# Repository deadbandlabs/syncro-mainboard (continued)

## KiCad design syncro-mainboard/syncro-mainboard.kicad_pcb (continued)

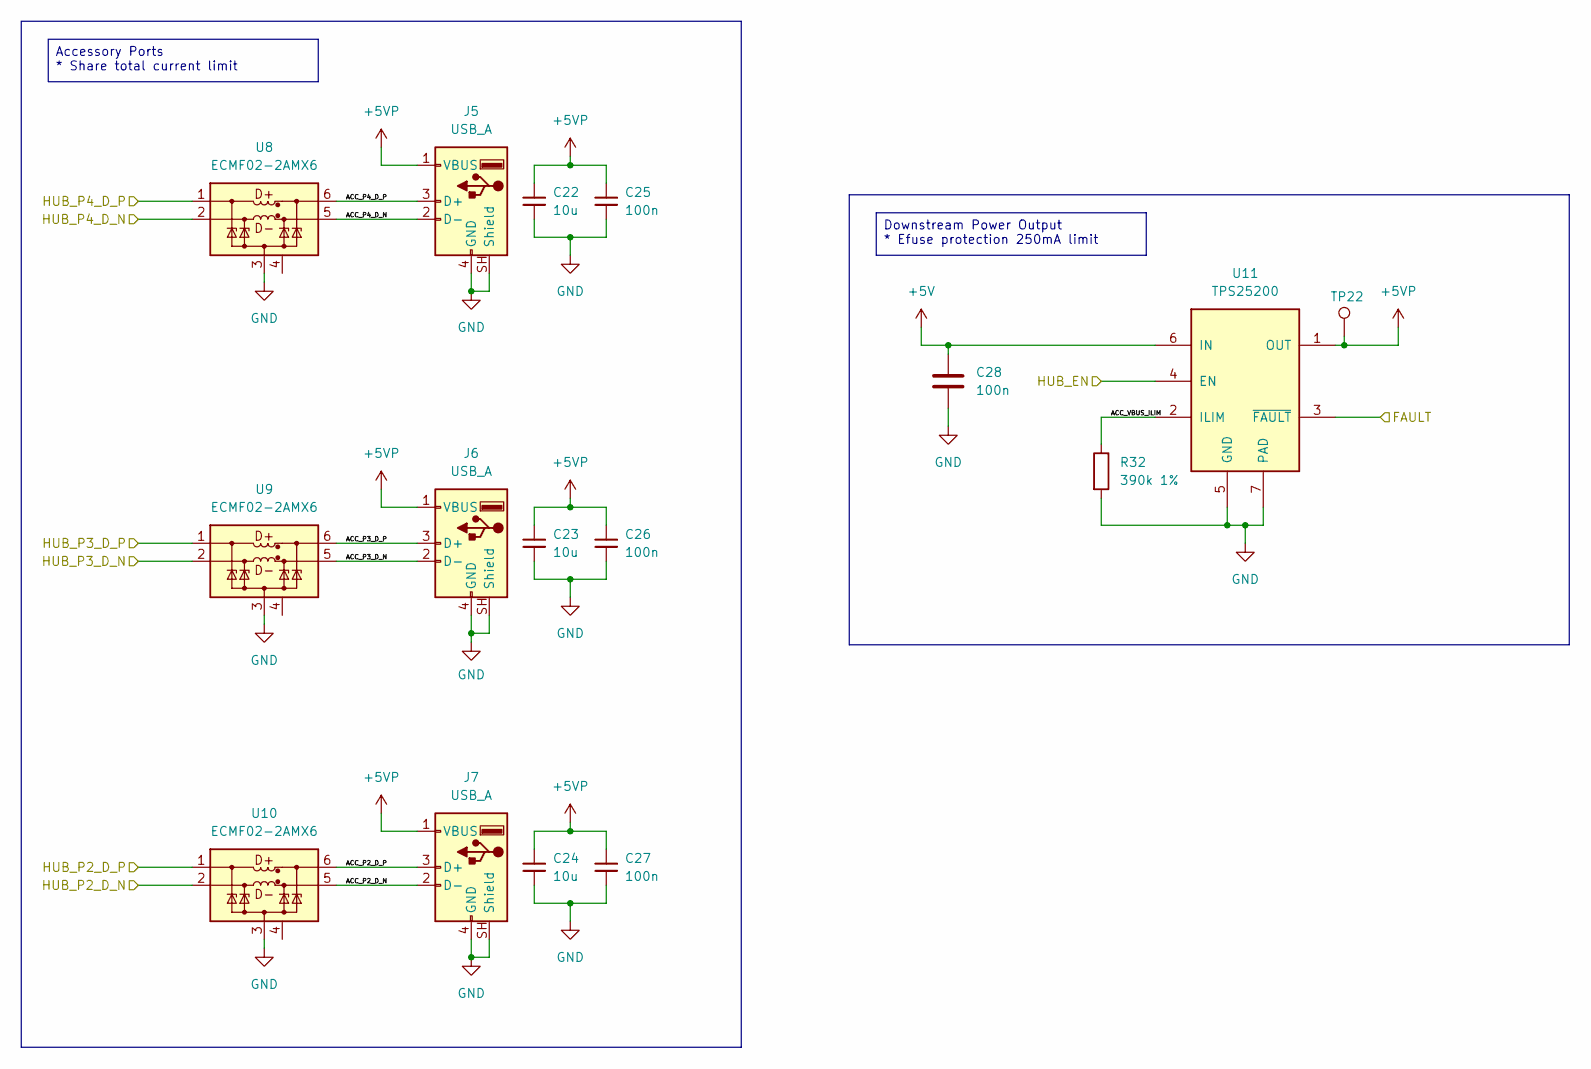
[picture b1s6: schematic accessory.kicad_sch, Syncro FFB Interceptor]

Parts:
C22, C23, C24: 10u; C_0805_2012Metric; LCSC C15850
C25, C26, C27, C28: 100n; C_0402_1005Metric; LCSC C1525
J5, J6, J7: USB_A; USB_A_SHOUHAN_10.0-QTJ6.3_Horizontal; LCSC C404966
R32: 390k 1%; R_0402_1005Metric; LCSC C25782
TP22: VUSB; TestPoint_Pad_D1.5mm
U8, U9, U10: ECMF02-2AMX6; ST_UQFN-6L_1.5x1.7mm_P0.5mm; MPN ECMF02-2AMX6; LCSC C2651144
U11: TPS25200; WSON-6-1EP_2x2mm_P0.65mm_EP1x1.6mm_ThermalVias_0.3mm; MPN TPS25200DRVR; LCSC C128401

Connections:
+5V: C28.1, U11.6 (IN); also elsewhere on the board
+5VP: C22.1, C23.1, C24.1, C25.1, C26.1, C27.1, J5.1 (VBUS), J6.1 (VBUS), J7.1 (VBUS), TP22.1 (1_1), U11.1 (OUT)
/STM32MP13 SOM/HUB_EN: U11.4 (EN); also elsewhere on the board
/USB Mux/HUB_FAULT: U11.3 (~FAULT); also elsewhere on the board
/USB Mux/USB Accessory Ports/ACC_P2_D_N: J7.2 (D-), U10.5 (D-_out)
/USB Mux/USB Accessory Ports/ACC_P2_D_P: J7.3 (D+), U10.6 (D+_out)
/USB Mux/USB Accessory Ports/ACC_P3_D_N: J6.2 (D-), U9.5 (D-_out)
/USB Mux/USB Accessory Ports/ACC_P3_D_P: J6.3 (D+), U9.6 (D+_out)
/USB Mux/USB Accessory Ports/ACC_P4_D_N: J5.2 (D-), U8.5 (D-_out)
/USB Mux/USB Accessory Ports/ACC_P4_D_P: J5.3 (D+), U8.6 (D+_out)
/USB Mux/USB Accessory Ports/ACC_VBUS_ILIM: R32.1, U11.2 (ILIM)
/USB Mux/USB Accessory Ports/HUB_P2_D_N: U10.2 (D-_in); also elsewhere on the board
/USB Mux/USB Accessory Ports/HUB_P2_D_P: U10.1 (D+_in); also elsewhere on the board
/USB Mux/USB Accessory Ports/HUB_P3_D_N: U9.2 (D-_in); also elsewhere on the board
/USB Mux/USB Accessory Ports/HUB_P3_D_P: U9.1 (D+_in); also elsewhere on the board
/USB Mux/USB Accessory Ports/HUB_P4_D_N: U8.2 (D-_in); also elsewhere on the board
/USB Mux/USB Accessory Ports/HUB_P4_D_P: U8.1 (D+_in); also elsewhere on the board
GND: C22.2, C23.2, C24.2, C25.2, C26.2, C27.2, C28.2, J5.4 (GND), J5.SH (Shield), J6.4 (GND), J6.SH (Shield), J7.4 (GND), J7.SH (Shield), R32.2, U8.3 (GND), U9.3 (GND), U10.3 (GND), U11.5 (GND), U11.7 (PAD); also elsewhere on the board

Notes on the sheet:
Accessory Ports * Share total current limit
Downstream Power Output * Efuse protection 250mA limit

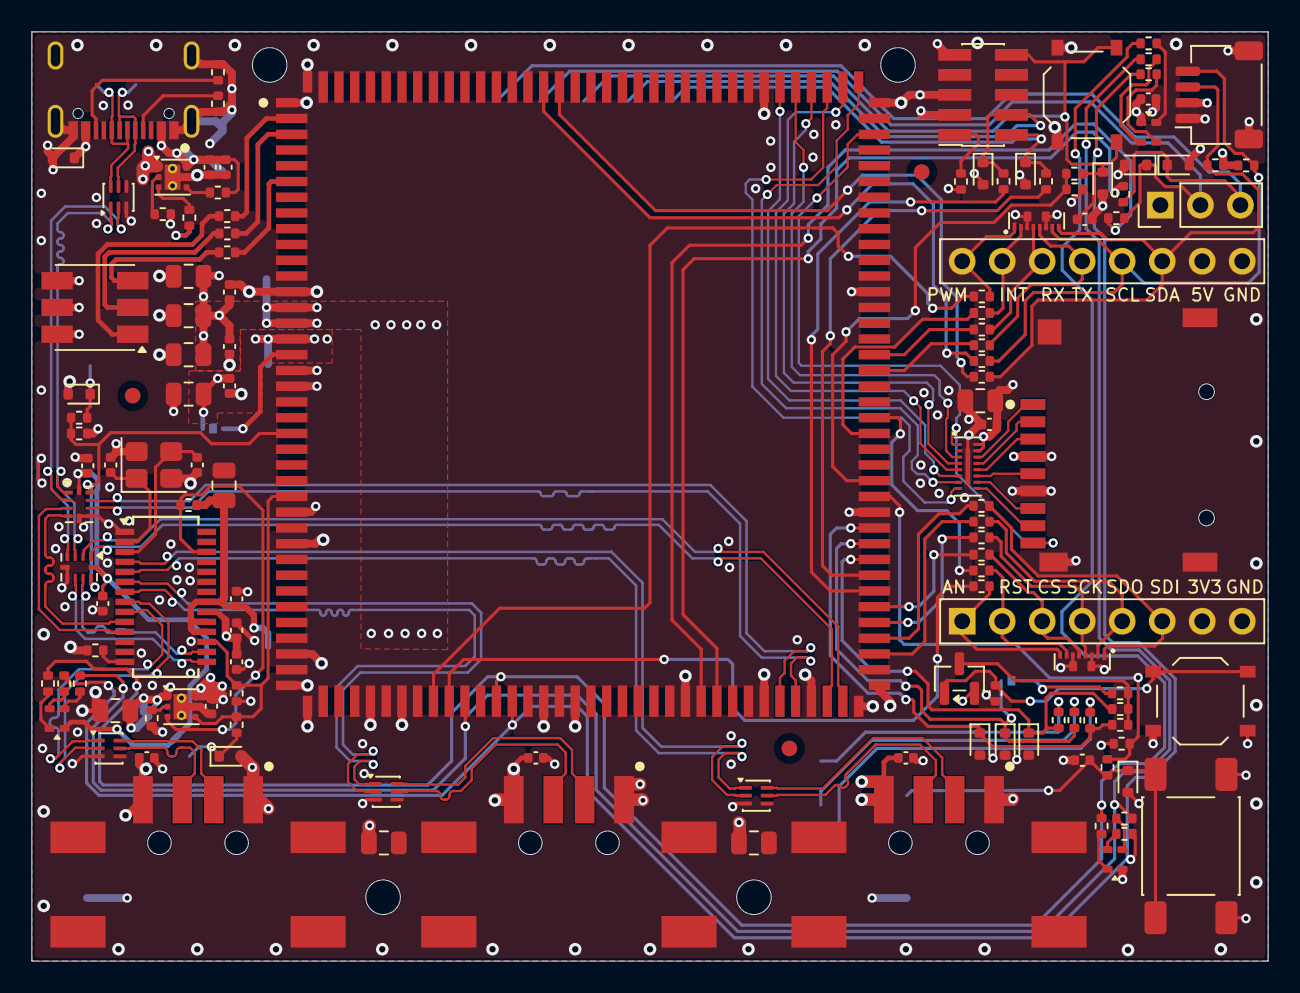
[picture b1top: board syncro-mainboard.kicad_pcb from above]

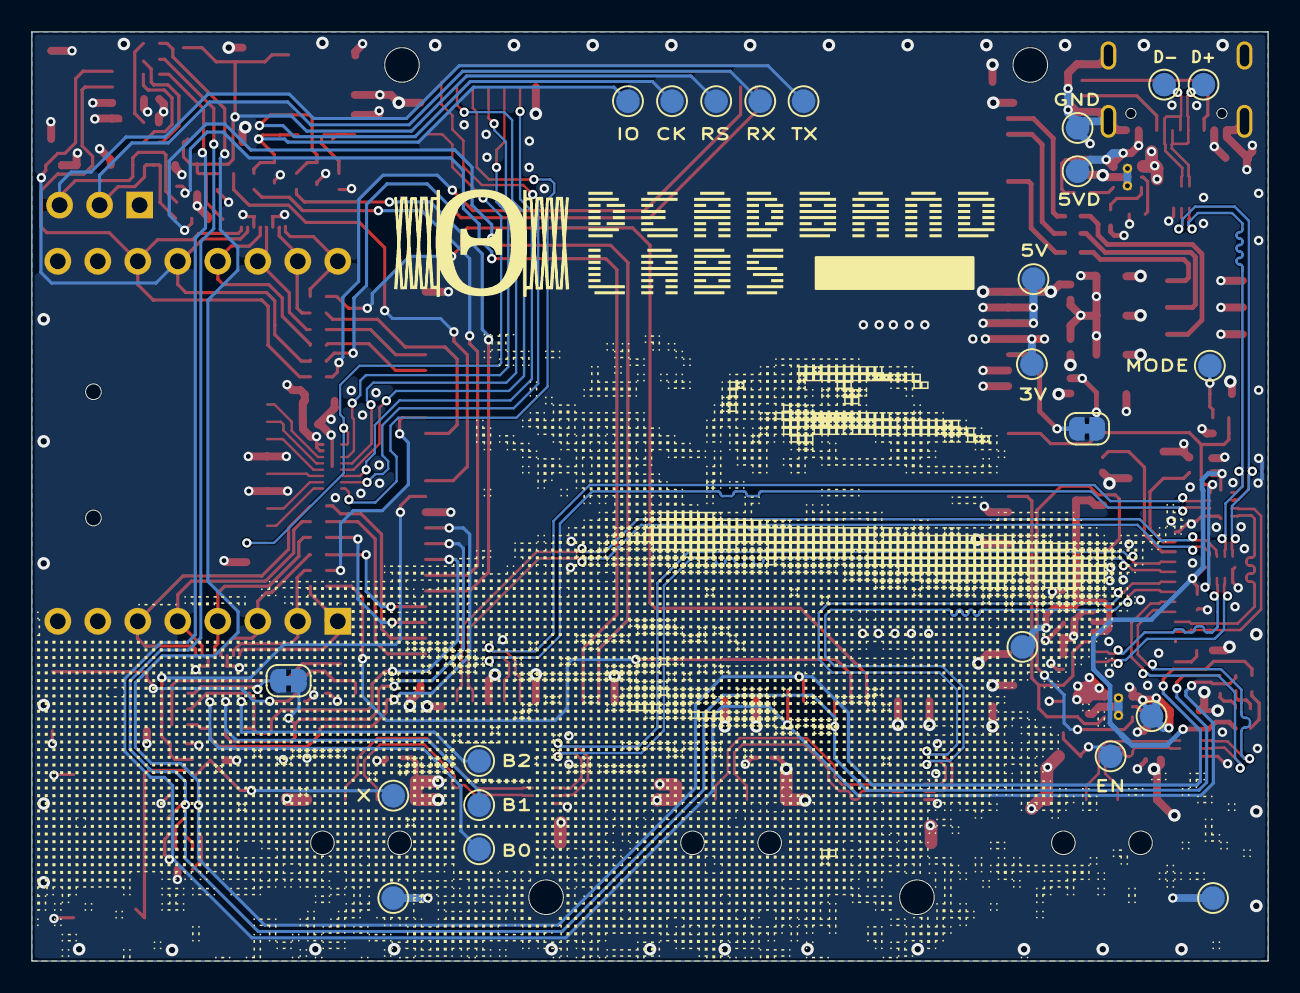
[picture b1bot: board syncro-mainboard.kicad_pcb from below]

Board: 4 copper layers, 78.5 x 59.0 mm, 149 parts (23 on the bottom side), 123 nets.
